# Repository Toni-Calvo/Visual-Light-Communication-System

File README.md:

# 📡 Visual Light Communication System

A visual light communication system developed and designed to be used as ambient light. It uses two Arduinos to modulate and demodulate light transmissions at a high frequency so the user does not experience light flickering. This system can be used in any building requiring Wi-Fi coverage where structural layouts create areas with poor signal.

---

## 📋 How to Use

To use the system, upload the file `transmitter\tx_code\tx_code.ino` to one Arduino and the file `receiver\rx_code\rx_code.ino` to another. Then, follow one of two options to build the transmitter and receiver modules:

---

### __1. Using a PCB Model:__
To use a PCB model, utilize the fabrication files located under `transmitter\transmitter_board\fab_files` and `receiver\receiver_board\fab_files` to build both boards:

**<u>Transmitter Board:</u>**

The pins on the PCB are, from top to bottom: Power, Ground, and Signal. The signal pin connects to Arduino digital pin 13.

**<u>Receiver Board:</u>**

The receiver module requires a solar panel on the empty slot at the top. The pins on the PCB are, from left to right: Ground, Power (1V), Power (5V), and Signal. The signal pin connects to Arduino digital pin 2.

---

### __2. Building Your Own Module:__

By following the schematics, you can build the circuit on a protoboard or similar (this is how we tested our system).

> [!WARNING]
> Ensure that both 10Ω resistors in the transmitter module (left) are rated to withstand the required power without overheating.

Once everything is connected, start both Arduinos. Any message written through the serial port of the transmitter Arduino will be displayed through the serial port of the receiver Arduino.

> [!NOTE]
> The modulation algorithm is designed to work with individual uppercase and lowercase alphabetical characters, so words are transmitted character by character.

> [!CAUTION]
> If no data is received, or the data received is not the same as the one sent, ensure the solar panel receives sufficient light from the LED and that ambient light, such as solar, is not interfering.

---

## 🔮 Future Improvements
* Add the possibility to regulate the light intensity (Pulse Duty Cycle).
* Allow bidirectional communication.
* Enable the transmission of non-alphabetical characters.
* Test the system with more than one receiver.
* Add protocols for data transmission to increase the complexity and scale of the system.

---

## ⚖ License
MIT License 2025 - [Toni Calvo Belmonte](https://github.com/Toni-Calvo). Take a look at the [LICENSE.md](LICENSE.md) for more information.

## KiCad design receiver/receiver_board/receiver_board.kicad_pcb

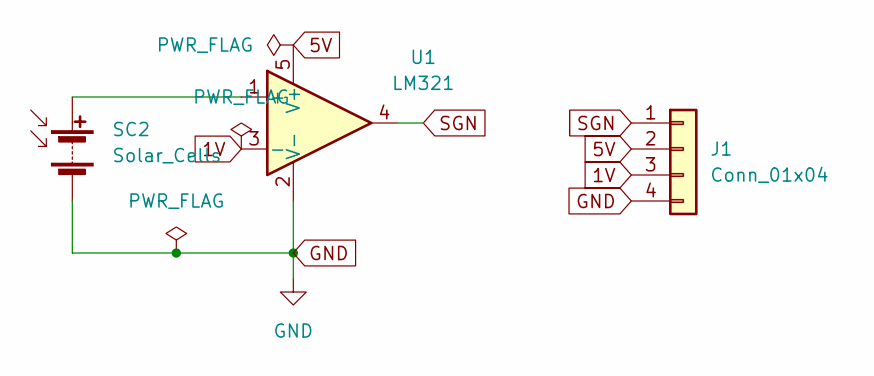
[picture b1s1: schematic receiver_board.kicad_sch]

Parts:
J1: Conn_01x04; PinHeader_1x04_P2.54mm_Horizontal
SC2: Solar_Cells; SolarCell_15mmx50mm_4PAD
U1: LM321; SOT-23-5

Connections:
1V: J1.3, U1.3 (-)
5V: J1.2, U1.5 (V+)
GND: J1.4, SC2.2 (-), U1.2 (V-)
unnamed: SC2.1 (+), U1.1 (+)
SGN: J1.1, U1.4

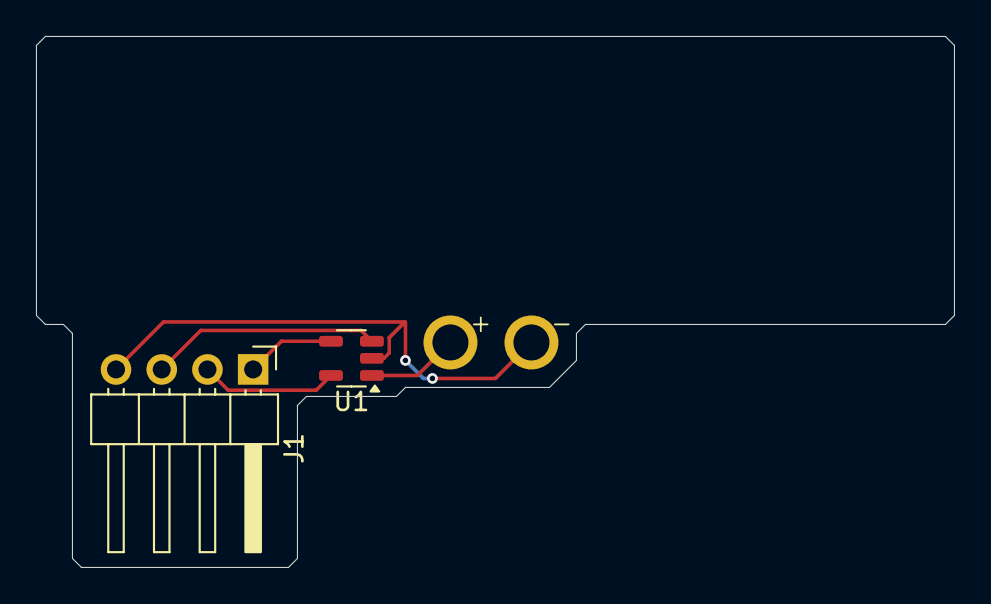
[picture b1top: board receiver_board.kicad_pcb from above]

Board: 2 copper layers, 51.0 x 29.5 mm, 3 parts (0 on the bottom side), 5 nets.

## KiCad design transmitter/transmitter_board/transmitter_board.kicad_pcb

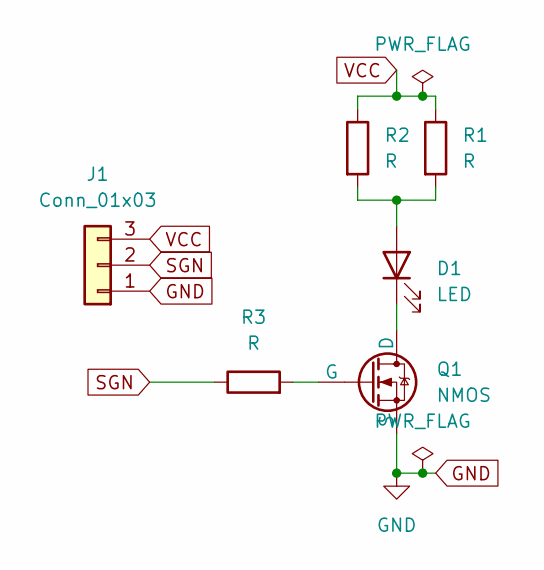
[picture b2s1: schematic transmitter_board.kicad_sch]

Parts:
D1: LED; LED_Cree-XHP50_6V
J1: Conn_01x03; PinHeader_1x03_P2.54mm_Vertical
Q1: NMOS; TO-220-3_Horizontal_TabDown
R1, R2: R; R_Axial_DIN0309_L9.0mm_D3.2mm_P12.70mm_Horizontal
R3: R; R_Axial_DIN0207_L6.3mm_D2.5mm_P7.62mm_Horizontal

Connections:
GND: J1.1, Q1.3 (S)
unnamed: D1.2 (A), R1.2, R2.2
unnamed: D1.1 (K), Q1.1 (D)
unnamed: Q1.2 (G), R3.2
SGN: J1.2, R3.1
VCC: J1.3, R1.1, R2.1

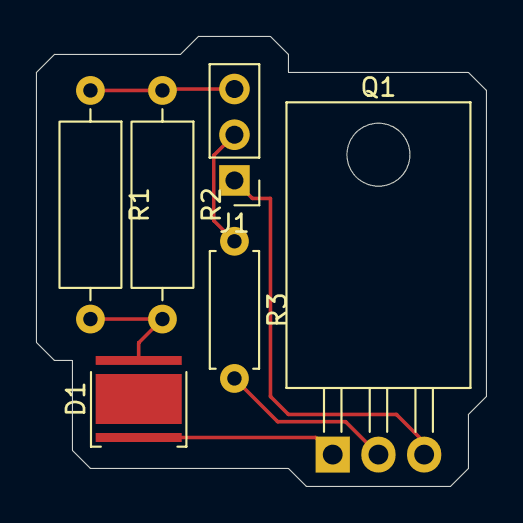
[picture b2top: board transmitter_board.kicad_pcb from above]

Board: 2 copper layers, 25.0 x 25.0 mm, 6 parts (0 on the bottom side), 6 nets.

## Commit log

2025-06-02 Transmitter Board
    Created the schematics for the transmitter board in kicad
2025-06-02 Receiver Board
    Created the schematics for the receiver board in KiCad.
2025-06-05 Re-Ordered components in PCB
    Moved components in KiCad to better view them.
2025-06-05 Transmitter Code
    Created the code for the arduino modulating the signals.
2025-06-08 Receiver Code
2025-06-22 LICENSE and README
2025-06-22 Update README.md
    Fixed identation in images.
